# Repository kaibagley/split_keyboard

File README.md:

# split_keyboard
Repo trying out KiCAD and designing a keyboard

Following the guide made by ai03 at: 
https://wiki.ai03.com/books/pcb-design/page/pcb-guide-part-1---preparations

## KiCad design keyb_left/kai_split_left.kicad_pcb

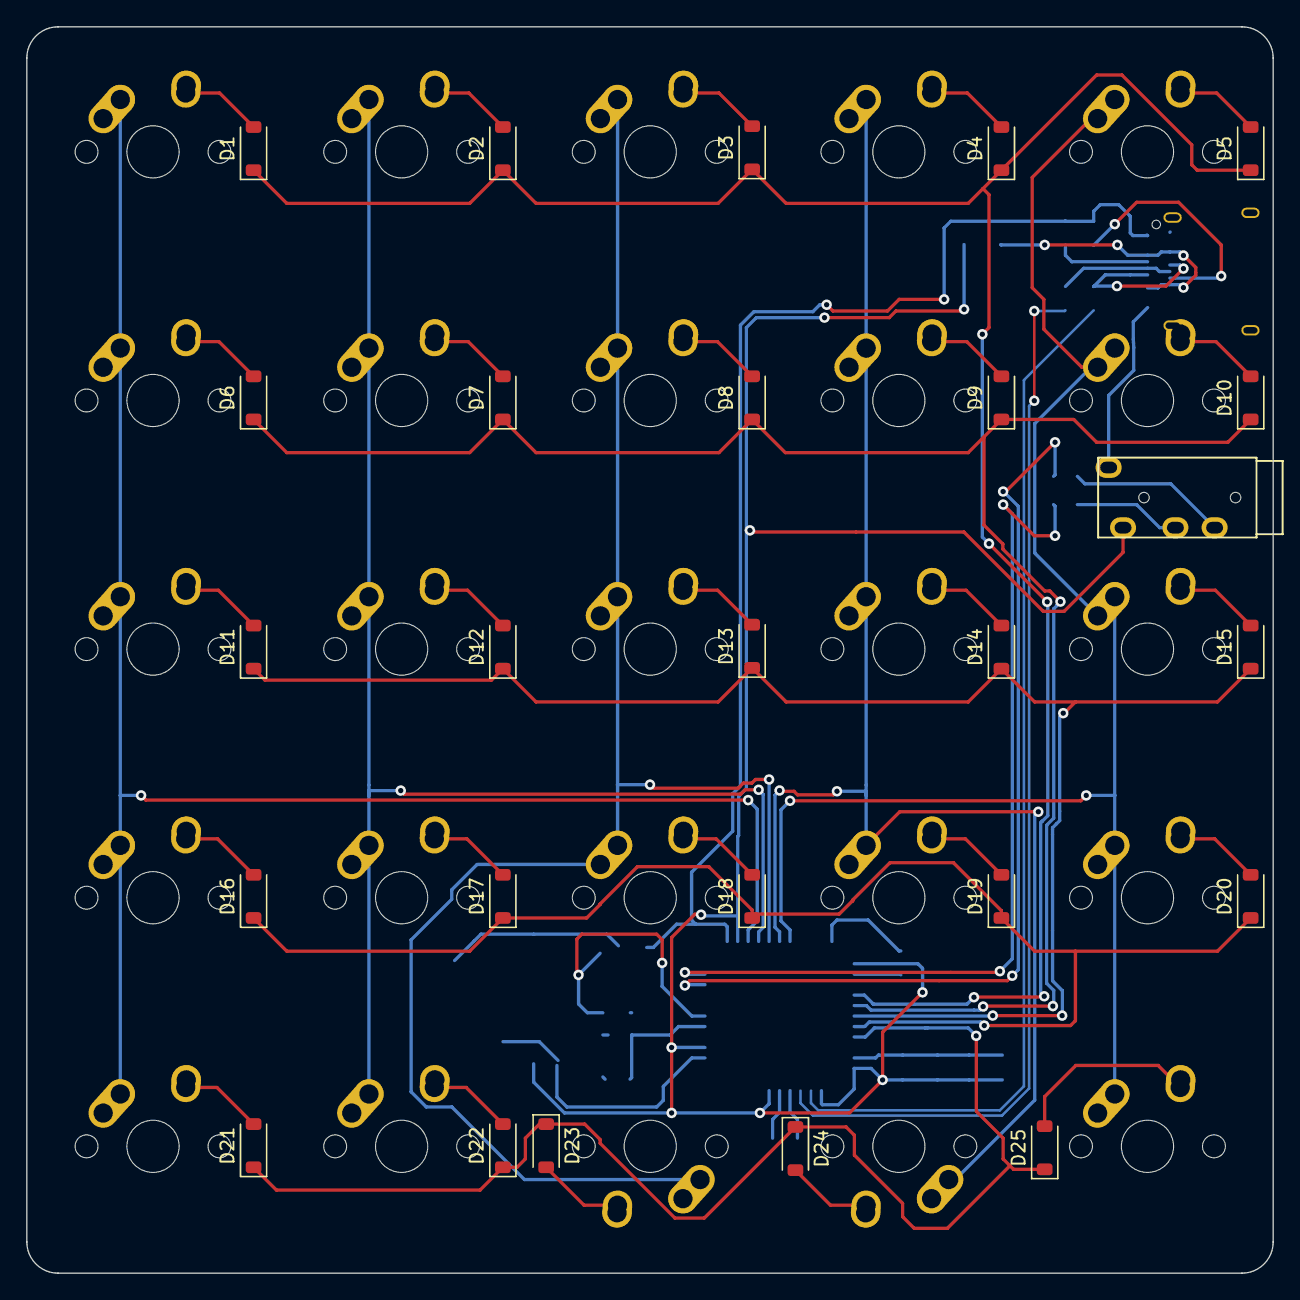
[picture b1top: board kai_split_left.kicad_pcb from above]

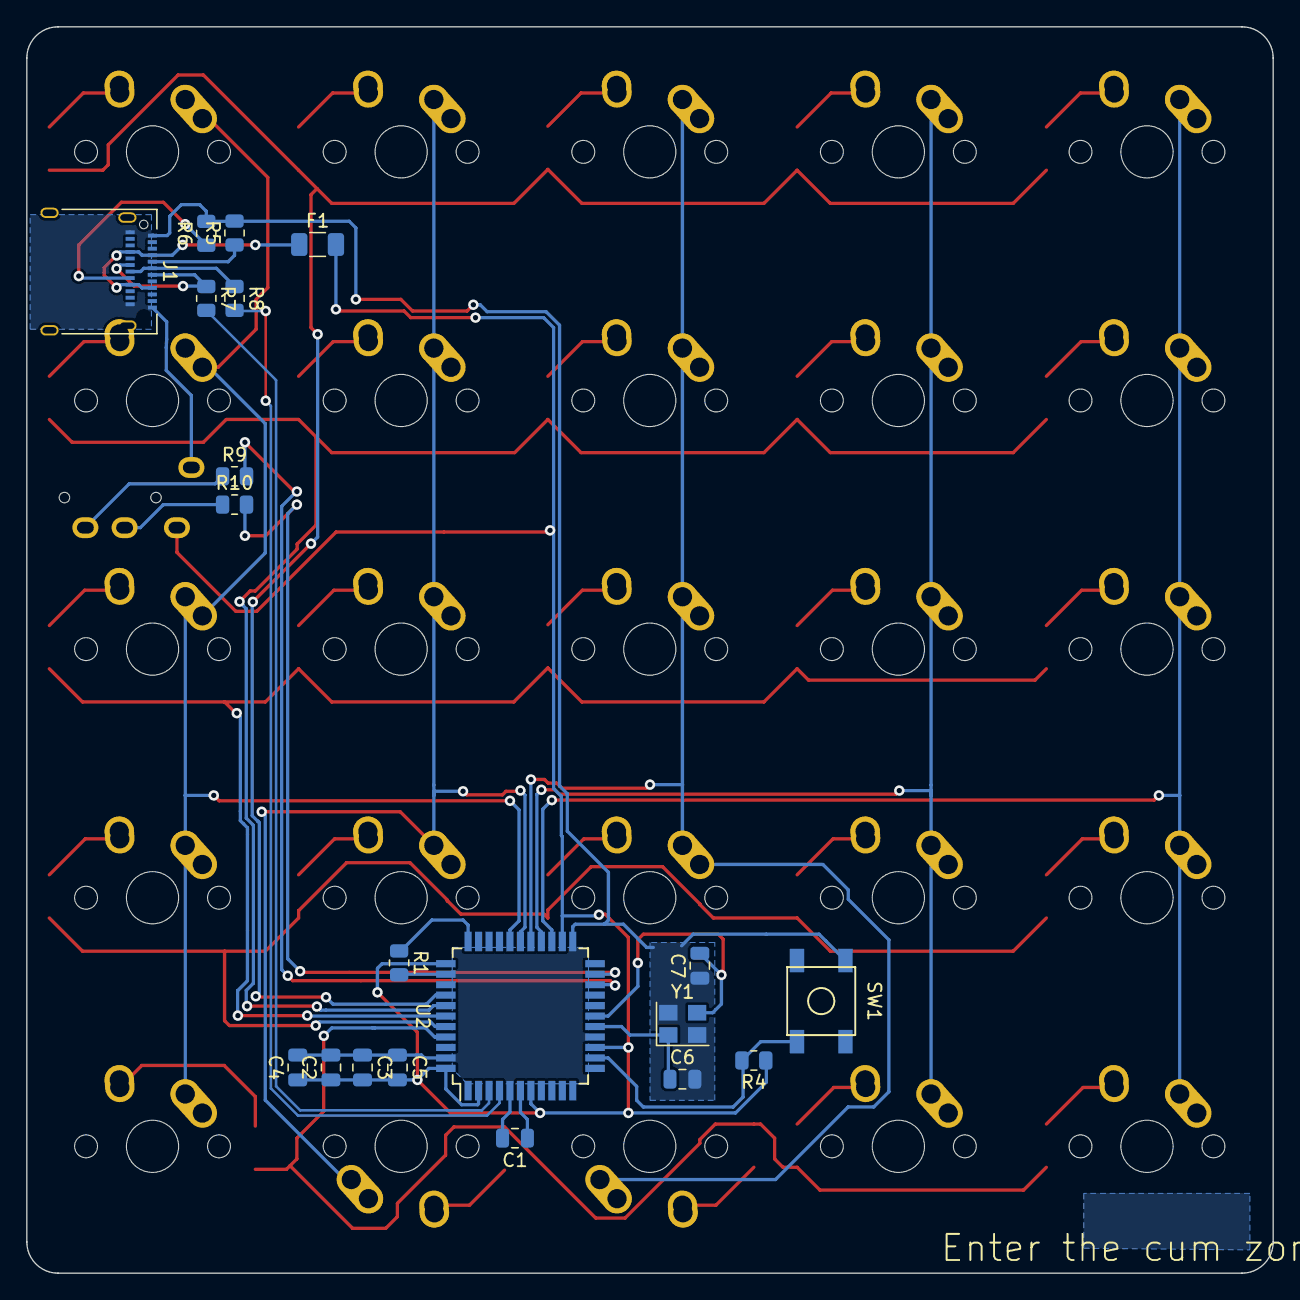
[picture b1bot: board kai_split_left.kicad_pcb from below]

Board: 2 copper layers, 95.2 x 95.2 mm, 71 parts (20 on the bottom side), 53 nets.

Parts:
C1: 1uF; C_0805_2012Metric
C2, C3, C4: 0.1uF; C_0805_2012Metric
C5: 10uF; C_0805_2012Metric
C6, C7: 22pF; C_0805_2012Metric
D1, D2, D3, D4, D5, D6, D7, D8, D9, D10, D11, D12, D13, D14, D15, D16, D17, D18, D19, D20, D21, D22, D23, D24, D25: SOD-123; D_SOD-123
F1: 500mA; Fuse_1206_3216Metric
J1: USB_C_Receptacle_USB2.0; USB_C_Receptacle_Amphenol_12401610E4-2A
J2: AudioJack4; TRRS-PJ-320A
MX1, MX2, MX3, MX4, MX5, MX6, MX7, MX8, MX9, MX10, MX11, MX12, MX13, MX14, MX15, MX16, MX17, MX18, MX19, MX20, MX21, MX22, MX23, MX24, MX25: MX-NoLED; MX-1U-NoLED
R1, R4: 10k; R_0805_2012Metric
R5, R6, R7, R8: 5.1k; R_0805_2012Metric
R9, R10: 1k; R_0805_2012Metric
SW1: SW_Push; SKQG-1155865
U2: ATmega32U4-A; TQFP-44_10x10mm_P0.8mm
Y1: 16MHz; Crystal_SMD_3225-4Pin_3.2x2.5mm

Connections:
+5V: C2.1, C3.2, C4.1, C5.2, F1.2, J2.2, R4.1, U2.2 (UVCC), U2.7 (VBUS), U2.14 (VCC), U2.24 (AVCC), U2.34 (VCC), U2.44 (AVCC)
COL0: MX1.1 (COL), MX6.1 (COL), MX11.1 (COL), MX16.1 (COL), MX21.1 (COL), U2.25 (PD4)
COL1: MX2.1 (COL), MX7.1 (COL), MX12.1 (COL), MX17.1 (COL), MX22.1 (COL), U2.26 (PD6)
COL2: MX3.1 (COL), MX8.1 (COL), MX13.1 (COL), MX18.1 (COL), MX23.1 (COL), U2.27 (PD7)
COL3: MX4.1 (COL), MX9.1 (COL), MX14.1 (COL), MX19.1 (COL), MX24.1 (COL), U2.28 (PB4)
COL4: MX5.1 (COL), MX10.1 (COL), MX15.1 (COL), MX20.1 (COL), MX25.1 (COL), U2.29 (PB5)
D+: R8.2, U2.4 (D+)
D-: R7.2, U2.3 (D-)
GND: C1.2, C2.2, C3.1, C4.2, C5.1, C6.2, C7.1, J1.A1 (GND), J1.A12 (GND), J1.B1 (GND), J1.B12 (GND), J2.1, R1.2, R5.2, R6.2, SW1.1, U2.5 (UGND), U2.15 (GND), U2.23 (GND), U2.35 (GND), U2.43 (GND), Y1.2, Y1.4
unnamed: D1.2 (A), MX1.2 (ROW)
unnamed: D2.2 (A), MX2.2 (ROW)
unnamed: D3.2 (A), MX3.2 (ROW)
unnamed: D4.2 (A), MX4.2 (ROW)
unnamed: D5.2 (A), MX5.2 (ROW)
unnamed: D6.2 (A), MX6.2 (ROW)
unnamed: D7.2 (A), MX7.2 (ROW)
unnamed: D8.2 (A), MX8.2 (ROW)
unnamed: D9.2 (A), MX9.2 (ROW)
unnamed: D10.2 (A), J1.S1 (SHIELD), MX10.2 (ROW)
unnamed: D11.2 (A), MX11.2 (ROW)
unnamed: D12.2 (A), MX12.2 (ROW)
unnamed: D13.2 (A), MX13.2 (ROW)
unnamed: D14.2 (A), MX14.2 (ROW)
unnamed: D15.2 (A), MX15.2 (ROW)
unnamed: D16.2 (A), MX16.2 (ROW)
unnamed: D17.2 (A), MX17.2 (ROW)
unnamed: D18.2 (A), MX18.2 (ROW)
unnamed: D19.2 (A), MX19.2 (ROW)
unnamed: D20.2 (A), MX20.2 (ROW)
unnamed: D21.2 (A), MX21.2 (ROW)
unnamed: D22.2 (A), MX22.2 (ROW)
unnamed: D23.2 (A), MX23.2 (ROW)
unnamed: D24.2 (A), MX24.2 (ROW)
unnamed: D25.2 (A), MX25.2 (ROW)
unnamed: J1.A5 (CC1), R5.1
unnamed: J1.B5 (CC2), R6.1
unnamed: J1.A6 (D+), J1.B6 (D+), R8.1
unnamed: J1.A7 (D-), J1.B7 (D-), R7.1
unnamed: J2.3, R10.1
unnamed: J2.4, R9.1
unnamed: C1.1, U2.6 (UCAP)
unnamed: C7.2, U2.17 (XTAL1), Y1.3
unnamed: C6.1, U2.16 (XTAL2), Y1.1
unnamed: R1.1, U2.33 (~HWB/PE2)
unnamed: R4.2, SW1.2, U2.13 (~RESET)
ROW0: D1.1 (K), D2.1 (K), D3.1 (K), D4.1 (K), D5.1 (K), U2.37 (PF6)
ROW1: D6.1 (K), D7.1 (K), D8.1 (K), D9.1 (K), D10.1 (K), U2.38 (PF5)
ROW2: D11.1 (K), D12.1 (K), D13.1 (K), D14.1 (K), D15.1 (K), U2.39 (PF4)
ROW3: D16.1 (K), D17.1 (K), D18.1 (K), D19.1 (K), D20.1 (K), U2.40 (PF1)
ROW4: D21.1 (K), D22.1 (K), D23.1 (K), D24.1 (K), D25.1 (K), U2.41 (PF0)
RX: R9.2, U2.20 (PD2)
TX: R10.2, U2.21 (PD3)
VCC: F1.1, J1.A4 (VBUS), J1.A9 (VBUS), J1.B4 (VBUS), J1.B9 (VBUS)

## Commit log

2023-03-12 initial kicad commit
2023-03-12 add submodules
2023-03-12 added libraries to kicad
2023-03-12 left and right halves of keeb put in seperate folders
2023-03-12 Left side only - assigned footprints
2023-03-12 added another library
2023-03-14 routing finsihed, very poorly
2023-03-14 basically done, only problem is that the quality is probably dog. Many other problems I can see too eg. the usb connector mounting point overlaps with a switch pole.
2023-03-14 Gerber files generated
